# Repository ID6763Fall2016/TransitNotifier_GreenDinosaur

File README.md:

# Transit Notifier - Green Dinosaur

This is the repository for the "Transit Tiles" Transit Notifier by Hareen Godthi and John Kimionis.
Read our blog post and wiki pages for description and setup instructions.

##Bill of Materials
Model Fabrication
* 1/16” chipboard (http://www.dickblick.com/products/crescent-chipboard-packs/)
* 1/16” clear acrylic (http://www.dickblick.com/products/acrylic-clear-sheets/)
* Spray paint in black, gray, red, and white (http://www.dickblick.com/search/?q=spray%20paint&x=0&y=0&sp_cs=UTF-8)
* Vellum (http://www.dickblick.com/products/canson-vidalon-vellum/)
* Spray adhesive (http://www.dickblick.com/products/elmers-spray-adhesive/)

Circuit
* 1 ESP8266-12E board (Amica NodeMCU) (https://www.amazon.com/HiLetgo-Version-NodeMCU-Internet-Development/dp/B010O1G1ES/)
* 1 USB-to-microUSB cable (https://www.amazon.com/AmazonBasics-Micro-USB-USB-2-0-Cable/dp/B00NH124VM/)
* 1 5V USB power bank (https://www.amazon.com/RAVPower-Smallest-Powerful-Portable-External/dp/B00ZZYBAI2/)
* 1 SMD 603 feed-through capacitor (http://www.digikey.com/product-detail/en/johanson-dielectrics-inc/100X14X105MV4T/709-1334-1-ND/2327234)
* 1 piece of FR1 board (https://www.amazon.com/sheets-Bakelite-phenol-laminate-microns/dp/B00IMG44PG/)

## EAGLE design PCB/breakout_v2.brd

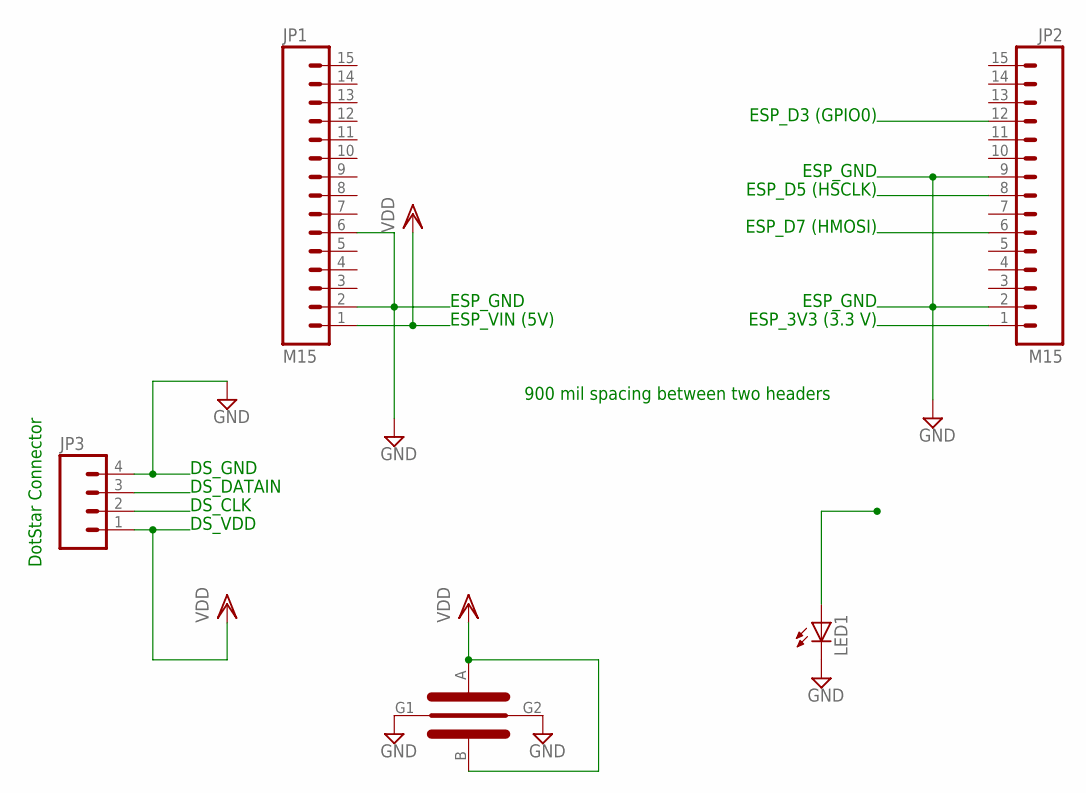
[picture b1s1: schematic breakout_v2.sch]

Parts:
JP1, JP2: M15; 1X15
JP3: M04PTH; 1X04
LED1: LED5MM
U$1: X2Y_CAP; 0603(X14)

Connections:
DS_CLK: JP2.8, JP3.2
DS_DATAIN: JP2.6, JP3.3
GND: JP1.2, JP1.6, JP2.2, JP2.9, JP3.4, LED1.K (C), U$1.G1, U$1.G2
LED_PIN: JP2.12, LED1.A
VDD: JP1.1, JP3.1, U$1.A, U$1.B

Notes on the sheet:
DotStar Connector
DS_GND
DS_DATAIN
DS_CLK
DS_VDD
ESP_GND
ESP_VIN (5V)
ESP_3V3 (3.3 V)
ESP_D7 (HMOSI)
ESP_D5 (HSCLK)
ESP_D3 (GPIO0)
900 mil spacing between two headers

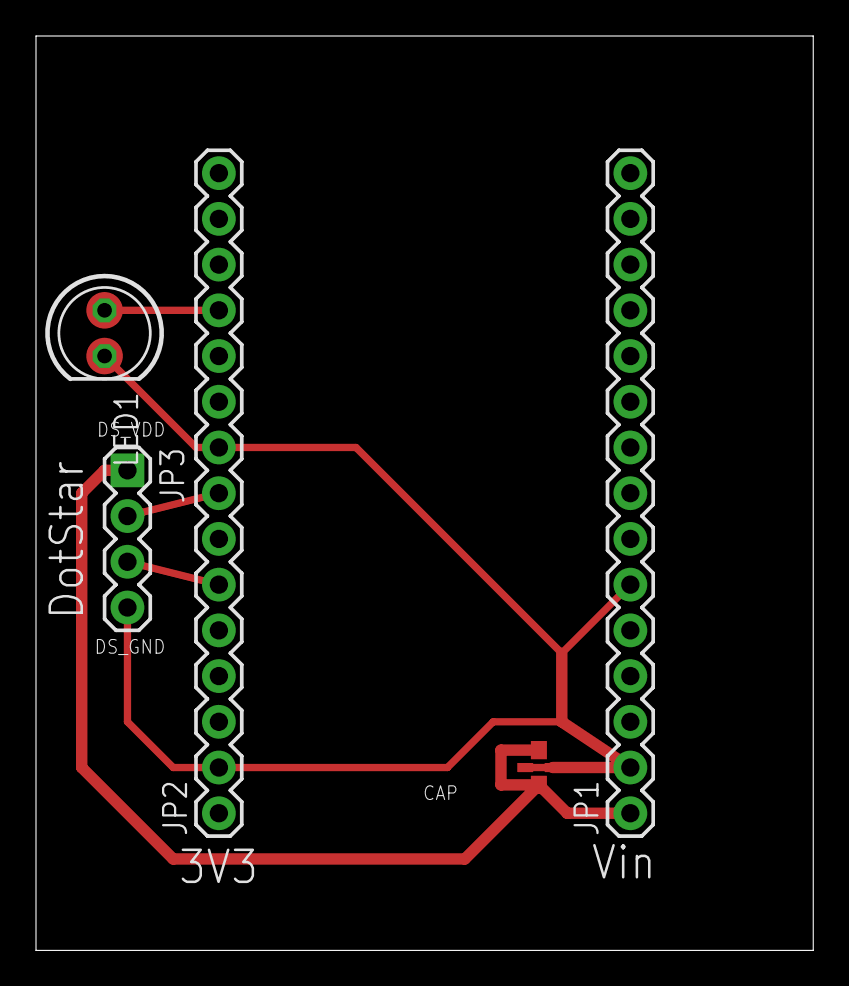
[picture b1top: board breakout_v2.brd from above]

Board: 2 copper layers, 43.2 x 50.8 mm, 5 parts (0 on the bottom side), 5 nets.

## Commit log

2016-10-31 readme
2016-10-31 photos
2016-10-31 design files
2016-10-31 add server
2016-10-31 client
2016-10-31 block diagram
2016-11-02 update BOM

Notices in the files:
parts and their libraries:
SparkFun-Connectors: Licensing: CC v3.0 Share-Alike You are welcome to use this library for commercial purposes.
